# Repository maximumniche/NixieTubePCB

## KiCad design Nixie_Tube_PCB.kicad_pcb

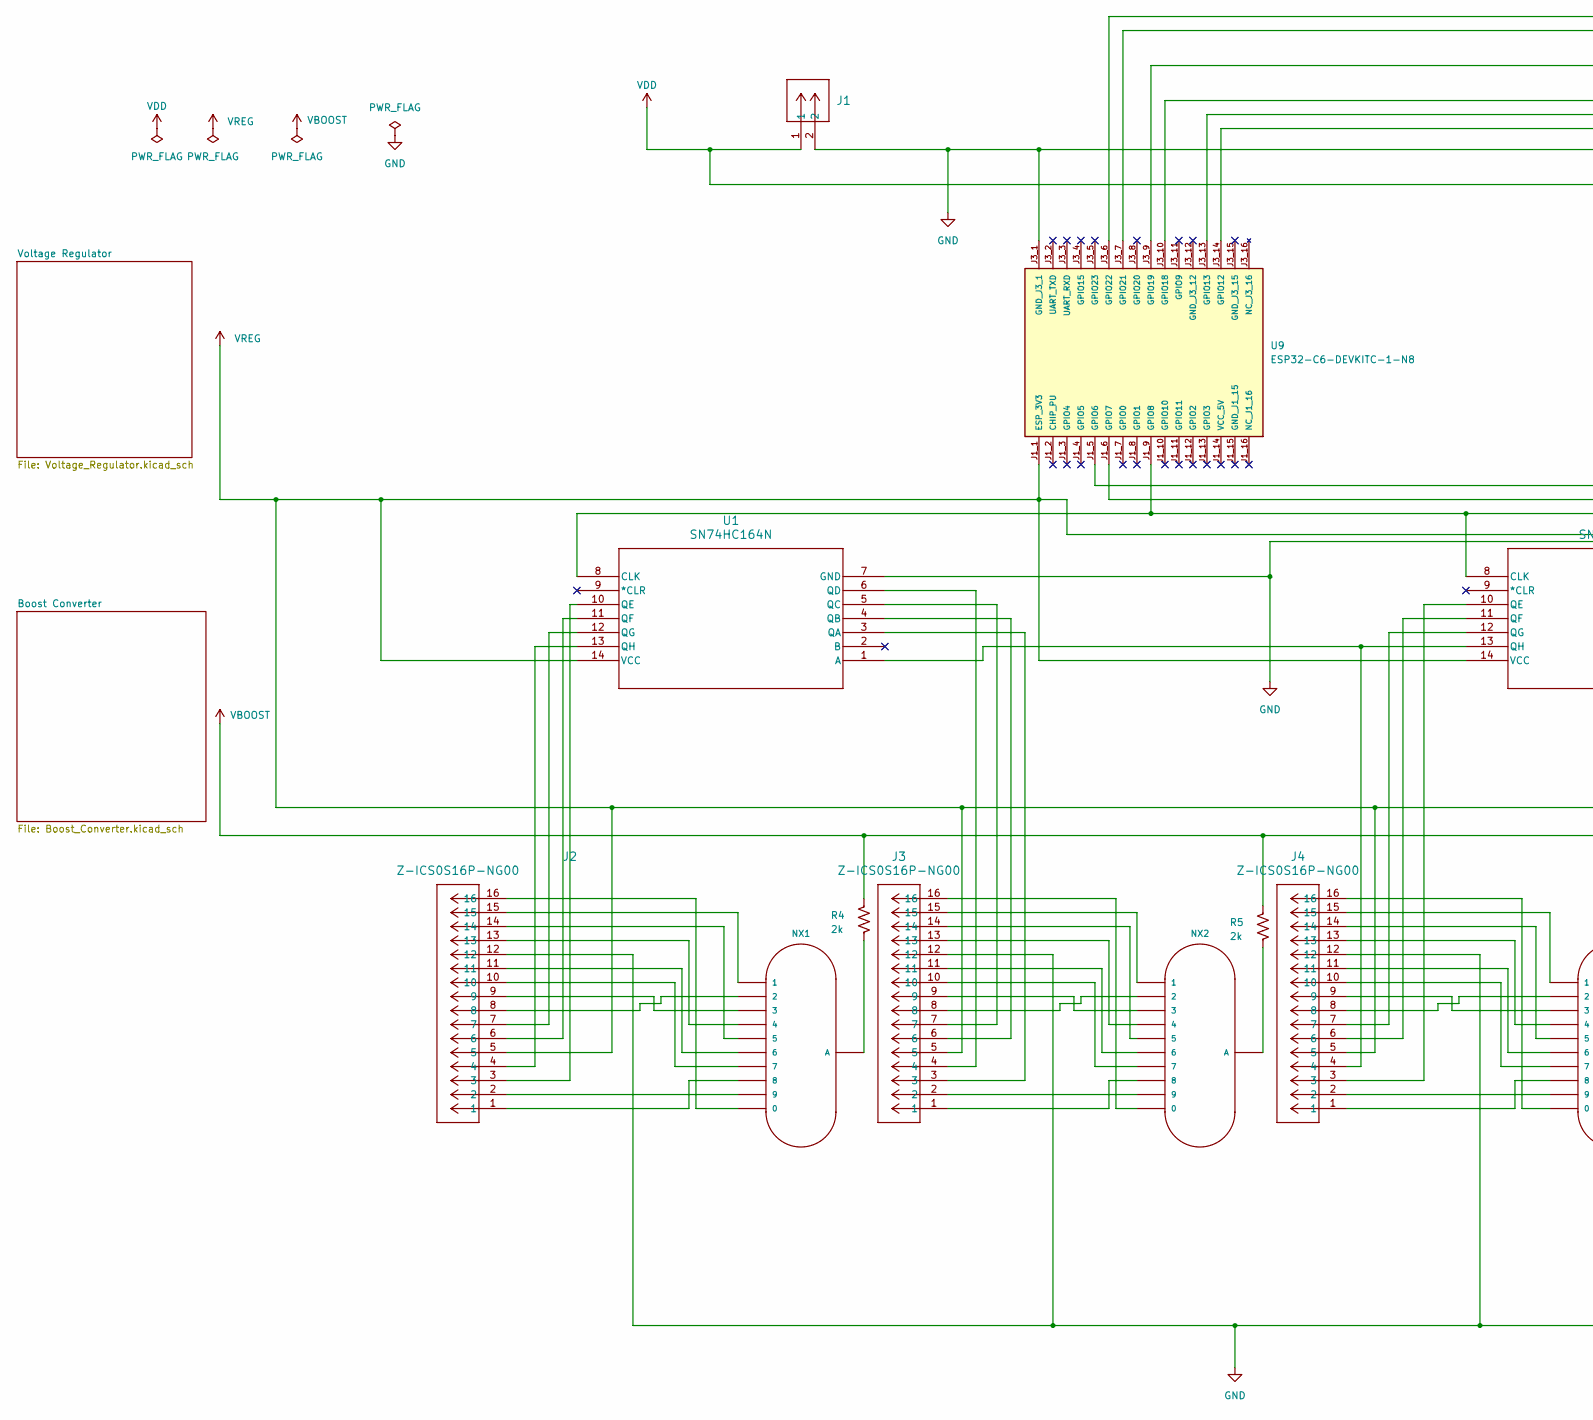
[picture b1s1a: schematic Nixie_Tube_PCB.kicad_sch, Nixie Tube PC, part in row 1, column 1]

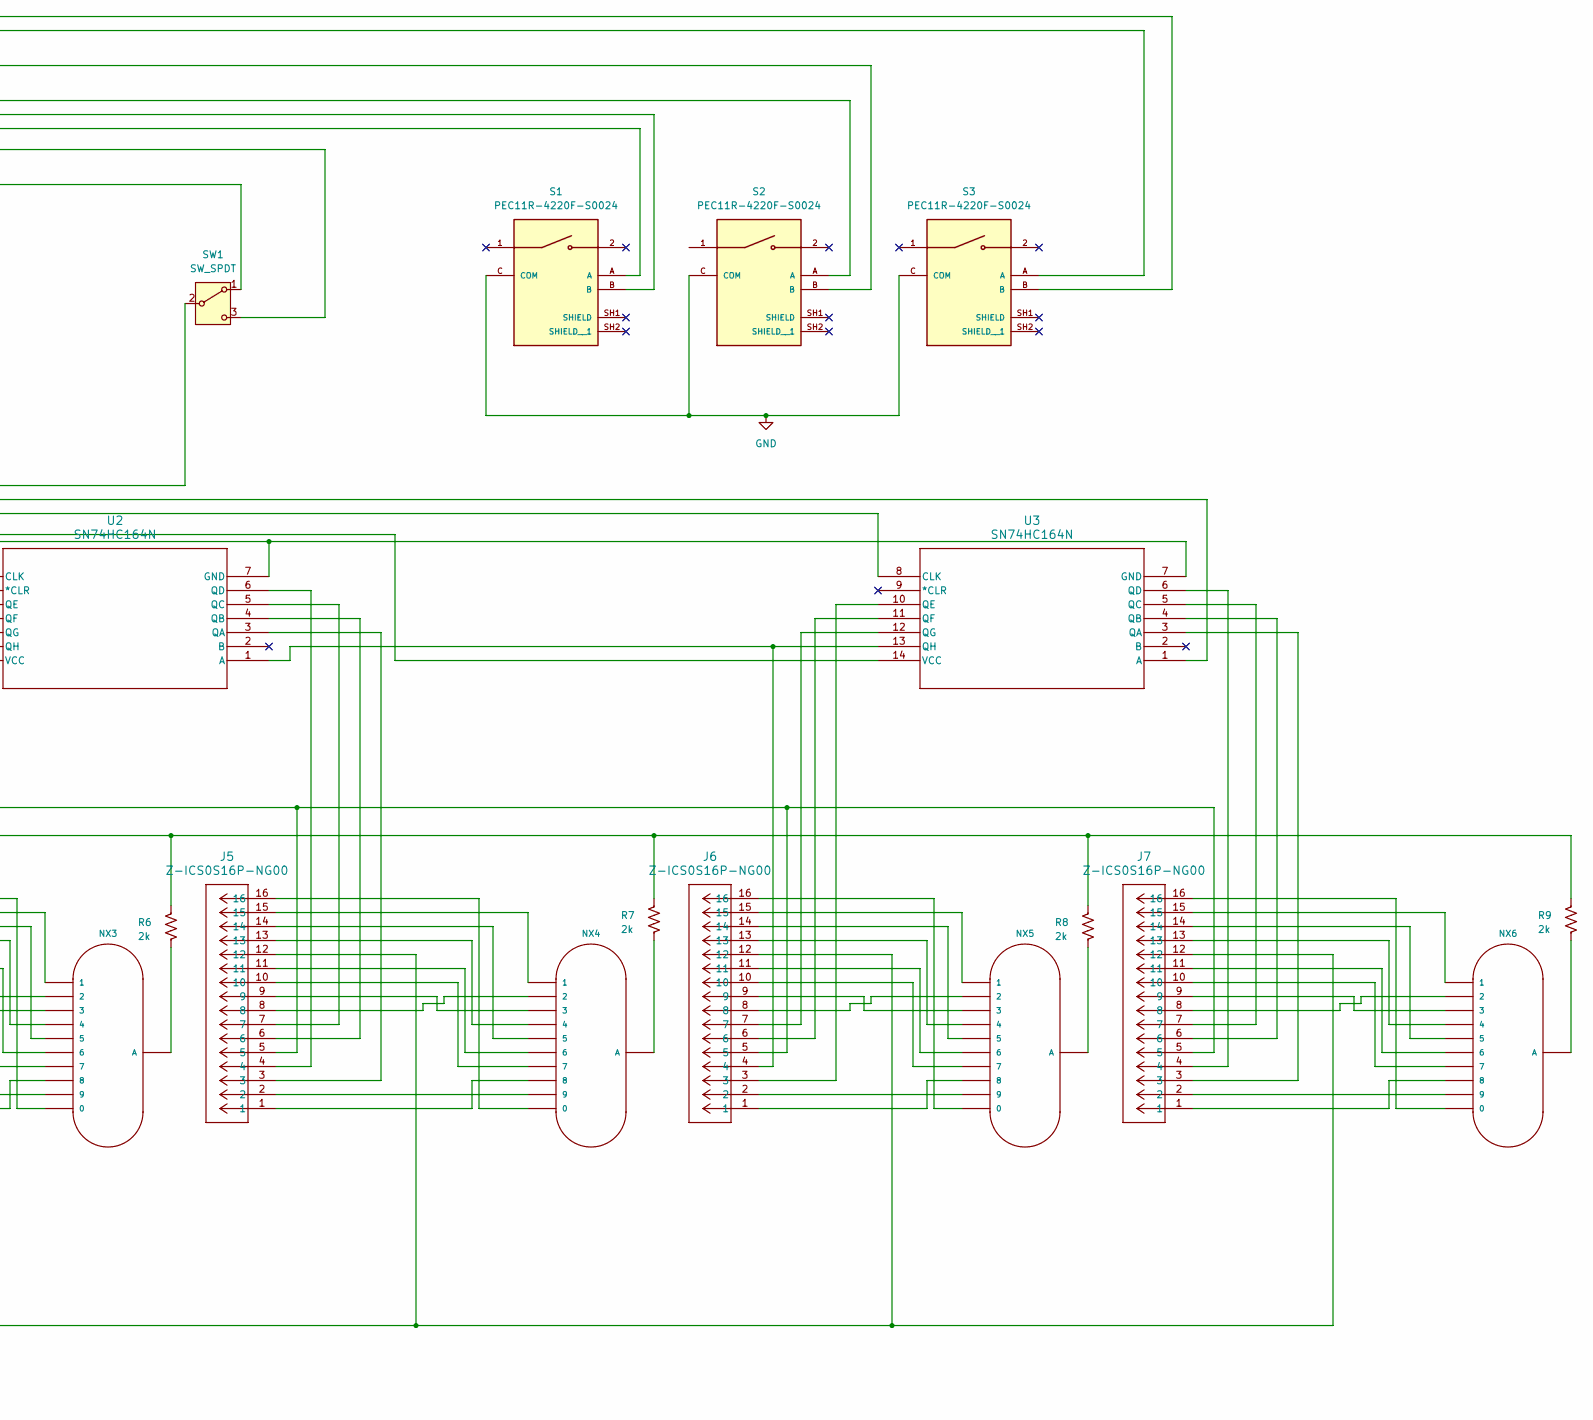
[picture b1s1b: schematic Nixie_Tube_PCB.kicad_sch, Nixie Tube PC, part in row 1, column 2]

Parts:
J1: DCJ200-10-A-K1-K; CONN3_DCJ200-10-A-K1-K_GCT
J2, J3, J4, J5, J6, J7: Z-ICS0S16P-NG00; CONN16-DIP_Z-ICS0S16P-NG00_CKM
NX1, NX2, NX3, NX4, NX5, NX6: IN-12A; IN-12
R4, R5, R6, R7, R8, R9: 2k; R_Axial_DIN0207_L6.3mm_D2.5mm_P10.16mm_Horizontal
S1, S2, S3: PEC11R-4220F-S0024; XDCR_PEC11R-4220F-S0024; PARTREV 11/23
SW1: SW_SPDT; SW_500SSP1S1M2REA
U1, U2, U3: SN74HC164N; N14
U9: ESP32-C6-DEVKITC-1-N8; MODULE_ESP32-C6-DEVKITC-1-N8; PARTREV 1.3

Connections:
GND: J1.2, J2.12, J3.12, J4.12, J5.12, J6.12, J7.12, S1.C (COM), S2.C (COM), S3.C (COM), SW1.3 (C), U1.7 (GND), U2.7 (GND), U3.7 (GND), U9.J3_1 (GND_J3_1); also elsewhere on the board
unnamed: J2.1, NX1.8
unnamed: J2.2, NX1.9
unnamed: J2.8, NX1.2
unnamed: J2.9, NX1.3
unnamed: J2.10, NX1.7
unnamed: J2.11, NX1.6
unnamed: J2.13, NX1.4
unnamed: J2.14, NX1.5
unnamed: J2.15, NX1.1
unnamed: J2.16, NX1.0
unnamed: J3.1, NX2.8
unnamed: J3.2, NX2.9
unnamed: J3.8, NX2.2
unnamed: J3.9, NX2.3
unnamed: J3.10, NX2.7
unnamed: J3.11, NX2.6
unnamed: J3.13, NX2.4
unnamed: J3.14, NX2.5
unnamed: J3.15, NX2.1
unnamed: J3.16, NX2.0
unnamed: J4.1, NX3.8
unnamed: J4.2, NX3.9
unnamed: J4.8, NX3.2
unnamed: J4.9, NX3.3
unnamed: J4.10, NX3.7
unnamed: J4.11, NX3.6
unnamed: J4.13, NX3.4
unnamed: J4.14, NX3.5
unnamed: J4.15, NX3.1
unnamed: J4.16, NX3.0
unnamed: J5.1, NX4.8
unnamed: J5.2, NX4.9
unnamed: J5.8, NX4.2
unnamed: J5.9, NX4.3
unnamed: J5.10, NX4.7
unnamed: J5.11, NX4.6
unnamed: J5.13, NX4.4
unnamed: J5.14, NX4.5
unnamed: J5.15, NX4.1
unnamed: J5.16, NX4.0
unnamed: J6.1, NX5.8
unnamed: J6.2, NX5.9
unnamed: J6.8, NX5.2
unnamed: J6.9, NX5.3
unnamed: J6.10, NX5.7
unnamed: J6.11, NX5.6
unnamed: J6.13, NX5.4
unnamed: J6.14, NX5.5
unnamed: J6.15, NX5.1
unnamed: J6.16, NX5.0
unnamed: J7.1, NX6.8
unnamed: J7.2, NX6.9
unnamed: J7.8, NX6.2
unnamed: J7.9, NX6.3
unnamed: J7.10, NX6.7
unnamed: J7.11, NX6.6
unnamed: J7.13, NX6.4
unnamed: J7.14, NX6.5
unnamed: J7.15, NX6.1
unnamed: J7.16, NX6.0
unnamed: NX1.A, R4.2
unnamed: NX2.A, R5.2
unnamed: NX3.A, R6.2
unnamed: NX4.A, R7.2
unnamed: NX5.A, R8.2
unnamed: NX6.A, R9.2
unnamed: SW1.2 (B), U9.J1_5 (GPIO6)
unnamed: J4.4, U1.1 (A), U2.13 (QH)
unnamed: U1.8 (CLK), U2.8 (CLK), U3.8 (CLK), U9.J1_9 (GPIO8)
unnamed: J3.3, U1.3 (QA)
unnamed: J3.6, U1.4 (QB)
unnamed: J3.7, U1.5 (QC)
unnamed: J3.4, U1.6 (QD)
unnamed: J2.3, U1.10 (QE)
unnamed: J2.6, U1.11 (QF)
unnamed: J2.7, U1.12 (QG)
unnamed: J2.4, U1.13 (QH)
unnamed: J6.4, U2.1 (A), U3.13 (QH)
unnamed: J5.3, U2.3 (QA)
unnamed: J5.6, U2.4 (QB)
unnamed: J5.7, U2.5 (QC)
unnamed: J5.4, U2.6 (QD)
unnamed: J4.3, U2.10 (QE)
unnamed: J4.6, U2.11 (QF)
unnamed: J4.7, U2.12 (QG)
unnamed: U3.1 (A), U9.J1_6 (GPIO7)
unnamed: J7.3, U3.3 (QA)
unnamed: J7.6, U3.4 (QB)
unnamed: J7.7, U3.5 (QC)
unnamed: J7.4, U3.6 (QD)
unnamed: J6.3, U3.10 (QE)
unnamed: J6.6, U3.11 (QF)
unnamed: J6.7, U3.12 (QG)
unnamed: S1.A, U9.J3_14 (GPIO12)
unnamed: S1.B, U9.J3_13 (GPIO13)
unnamed: S2.A, U9.J3_10 (GPIO18)
unnamed: S2.B, U9.J3_9 (GPIO19)
unnamed: S3.A, U9.J3_7 (GPIO21)
unnamed: S3.B, U9.J3_6 (GPIO22)
VBOOST: R4.1, R5.1, R6.1, R7.1, R8.1, R9.1; also elsewhere on the board
VDD: J1.1, SW1.1 (A); also elsewhere on the board
VREG: J2.5, J3.5, J4.5, J5.5, J6.5, J7.5, U1.14 (VCC), U2.14 (VCC), U3.14 (VCC), U9.J1_1 (ESP_3V3); also elsewhere on the board

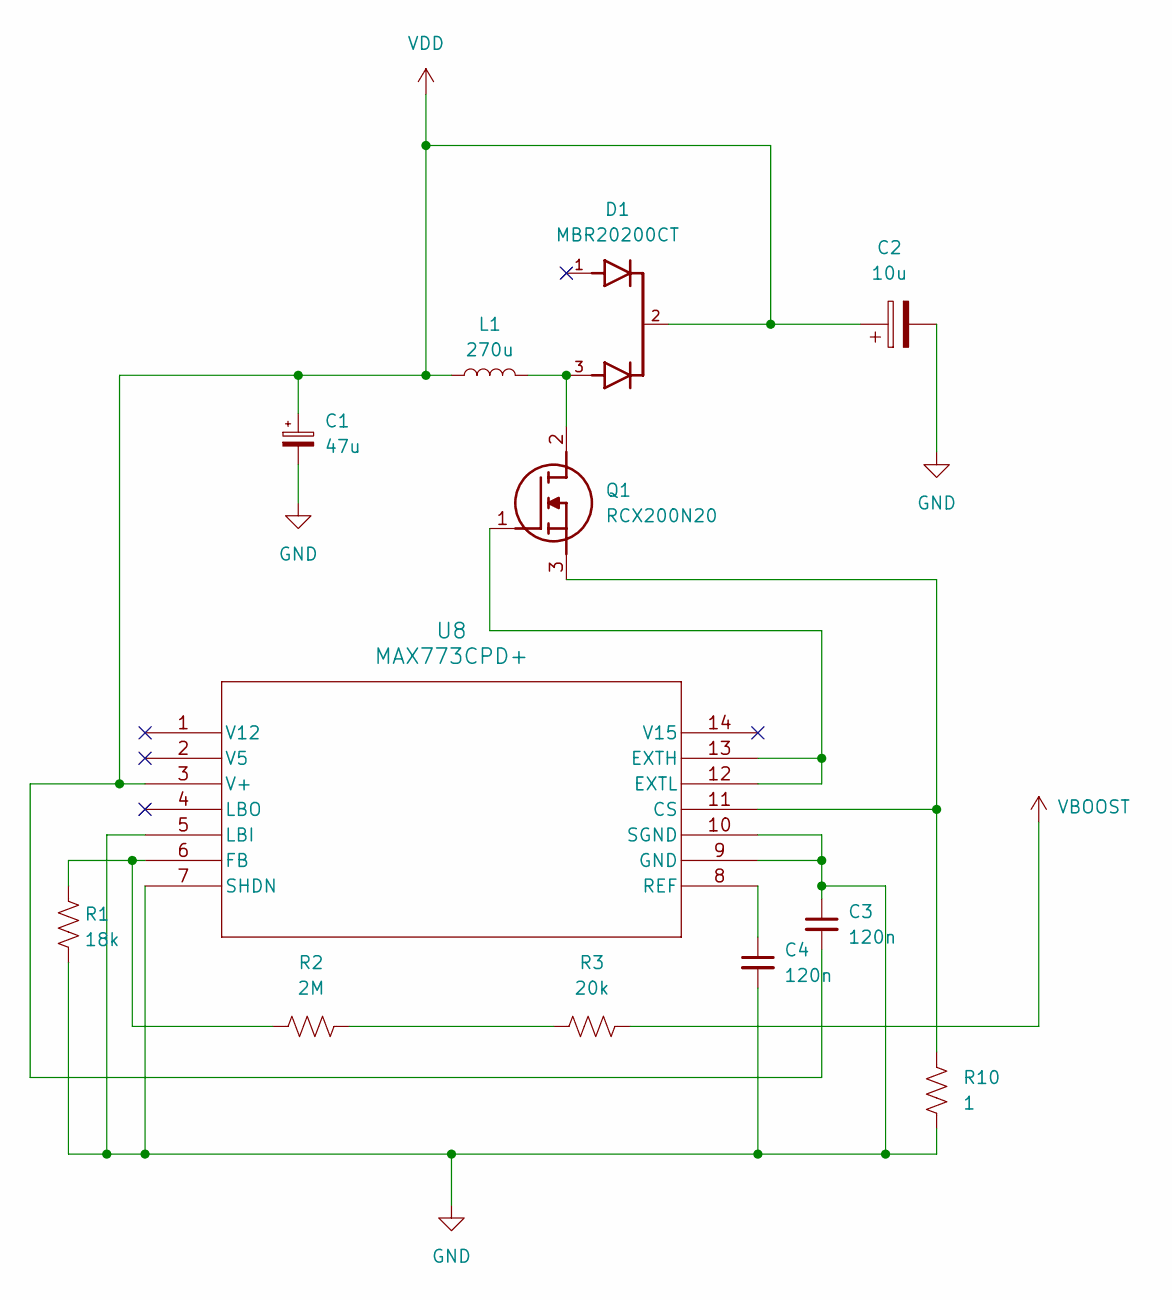
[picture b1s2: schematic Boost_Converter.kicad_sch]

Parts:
C1: 47u; CP_Wurth_WCAP-ATUL-P2.5D6.3L11
C2: 10u; CAP_EEUED_10X20_PAN
C3, C4: 120n; C_Disc_D5.0mm_W2.5mm_P5.00mm
D1: MBR20200CT; TO254P1050X476X2020-3; PARTREV G2104
L1: 270u; IND_BOURNS_RLB0914
Q1: RCX200N20; TO254P480X1010X1760-3P; Mouser Part Number 755-RCX200N20
R1: 18k; R_Axial_DIN0207_L6.3mm_D2.5mm_P10.16mm_Horizontal
R2: 2M; R_Axial_DIN0207_L6.3mm_D2.5mm_P10.16mm_Horizontal
R3: 20k; R_Axial_DIN0207_L6.3mm_D2.5mm_P10.16mm_Horizontal
R10: 1; R_Axial_DIN0207_L6.3mm_D2.5mm_P10.16mm_Horizontal
U8: MAX773CPD+; 21-0043D_14_MXM

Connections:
GND: C1.2, C2.2, C3.1, C4.2, R1.2, R10.2, U8.5 (LBI), U8.7 (SHDN), U8.9 (GND), U8.10 (SGND); also elsewhere on the board
unnamed: D1.3, L1.2, Q1.2 (D)
unnamed: Q1.1 (G), U8.12 (EXTL), U8.13 (EXTH)
unnamed: Q1.3 (S), R10.1, U8.11 (CS)
unnamed: R2.2, R3.1
unnamed: R1.1, R2.1, U8.6 (FB)
unnamed: C4.1, U8.8 (REF)
VBOOST: R3.2; also elsewhere on the board
VDD: C1.1, C2.1, C3.2, D1.2, L1.1, U8.3 (V+); also elsewhere on the board

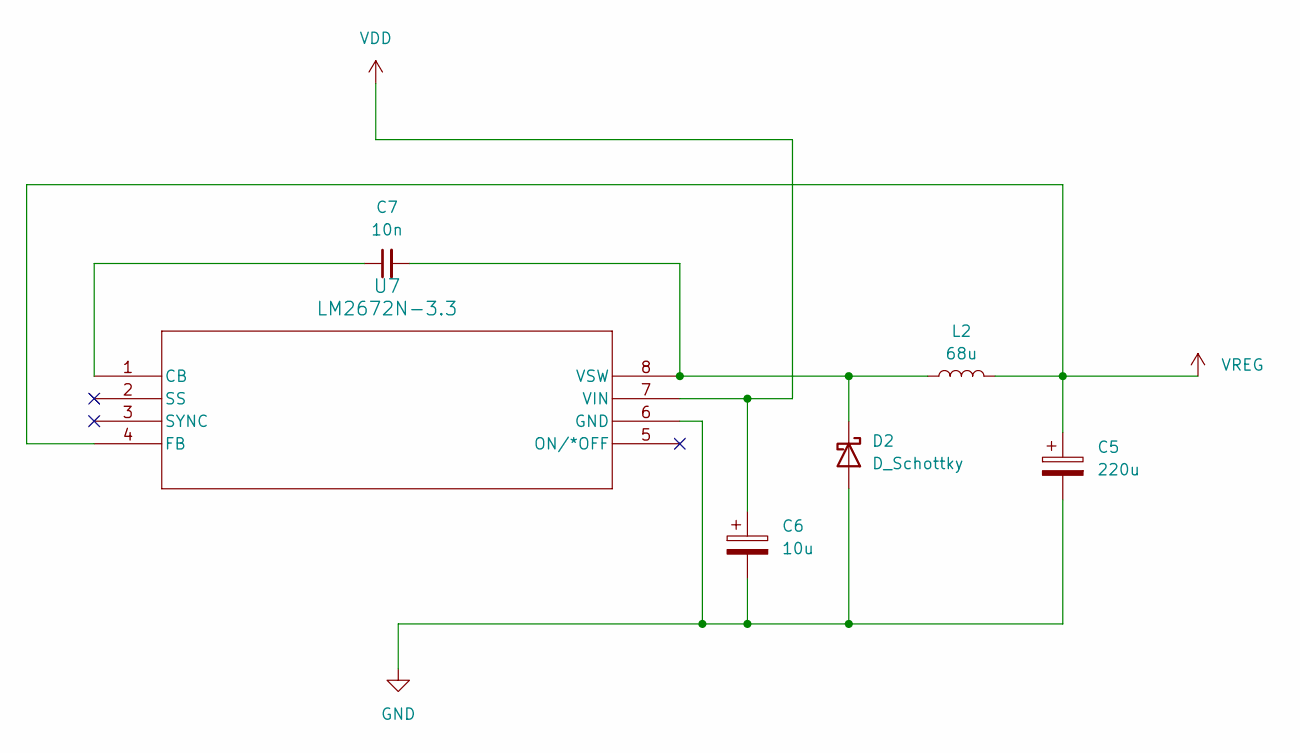
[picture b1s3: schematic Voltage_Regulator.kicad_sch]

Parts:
C5: 220u; CAP_YX_10X16_RUB
C6: 10u; CAP_EEUED_10X20_PAN
C7: 10n; C_Disc_D5.0mm_W2.5mm_P5.00mm
D2: D_Schottky; P1_DO-15
L2: 68u; L_Wurth_WE-TI-6065
U7: LM2672N-3.3; N08E_TEX

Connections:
GND: C5.2, C6.2, D2.2 (A), U7.6 (GND); also elsewhere on the board
unnamed: C7.2, D2.1 (K), L2.1, U7.8 (VSW)
unnamed: C7.1, U7.1 (CB)
VDD: C6.1, U7.7 (VIN); also elsewhere on the board
VREG: C5.1, L2.2, U7.4 (FB); also elsewhere on the board

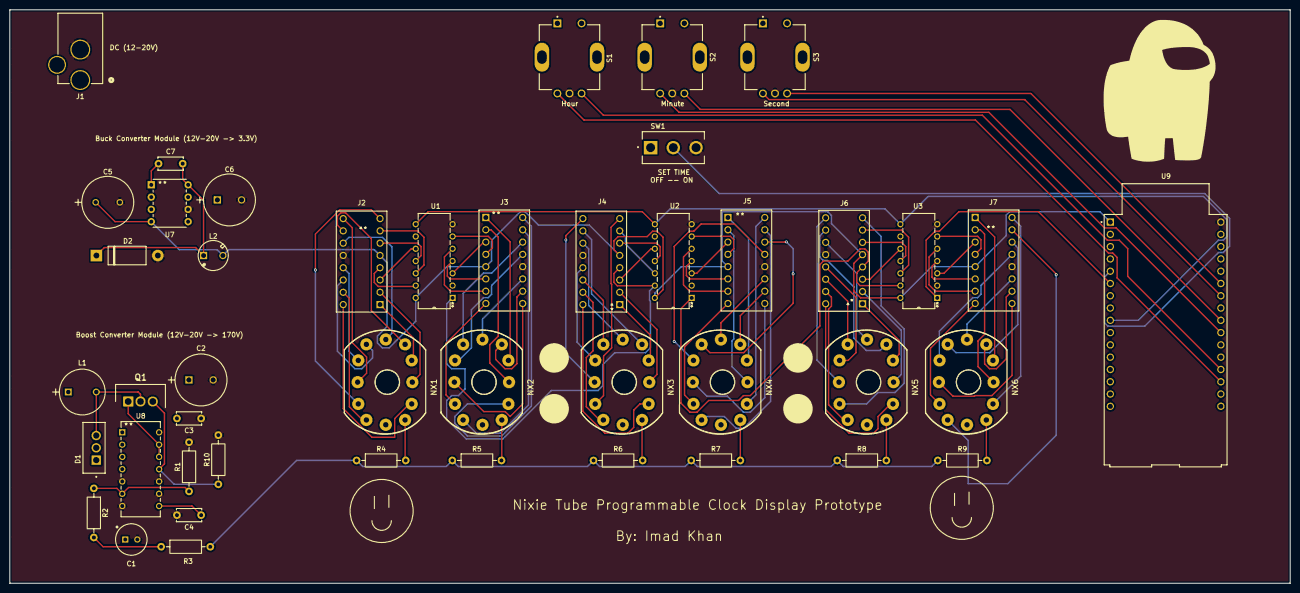
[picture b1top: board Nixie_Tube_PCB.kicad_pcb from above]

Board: 2 copper layers, 264.8 x 118.6 mm, 45 parts (0 on the bottom side), 111 nets.
